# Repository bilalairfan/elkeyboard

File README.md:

# elkeyboard

A 3x3 macropad I will primarily use for CADding and school work.

## Features
- 8 keys
- a rotary encoder
- 128x32 OLED display
- LEDs under each key

link to cad: https://cad.onshape.com/documents/f6566b1274e7edd1fcbf8569/w/f5617eb1dfdd9ed77d1d4c33/e/8ab57a133af5eb0a263a87d2?renderMode=0&uiState=69e41b9765a285248c64cd51

# Diagrams

### Schematic: 

### PCB: 

## Firmware
My layout is going to be based on my shortcuts for my cad software (onshape).
The bottom line is going to be general purpose shortcuts while the top
and middle are more specific to working on onshape. This is primarily
sketch constraints as I tend to forget my binds when I'm working. 
Additionally, I have an encoder binded to my volume as I tend to change my volume a lot between days and tasks.

## BOM:
- 8x cherry mx switches
- 8x keycaps
- 1x ec11 rotary encoder
- 9x sk6812 mini e
- 9x 1N4148 diodes
- 1x OLED .91" 128x32
- 1x XIAO RP2040
- 1x case

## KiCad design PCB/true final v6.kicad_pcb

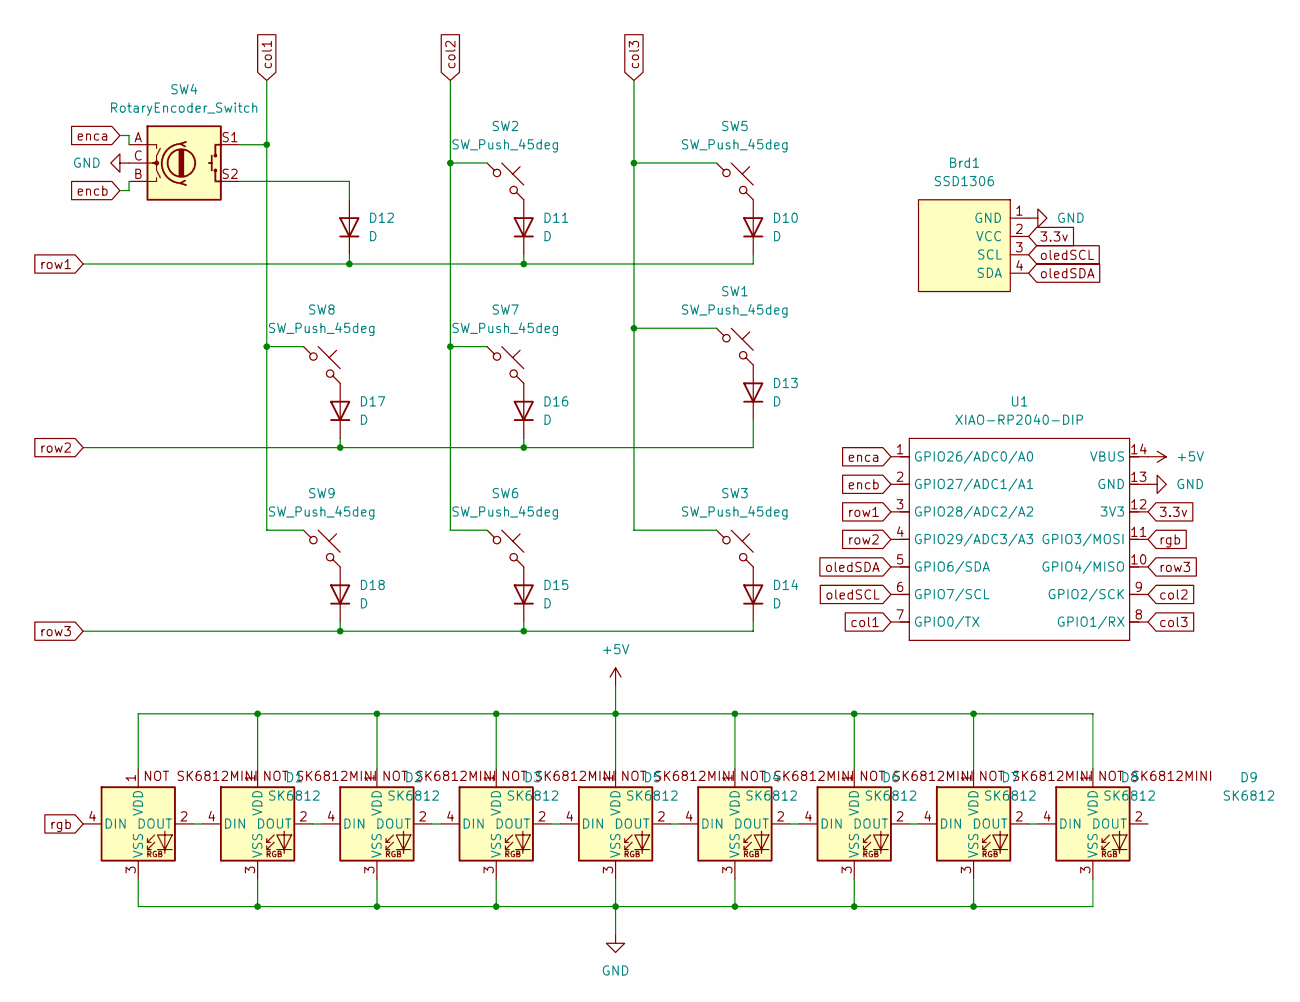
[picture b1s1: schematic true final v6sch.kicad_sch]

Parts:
Brd1: SSD1306; SSD1306-0.91-OLED-4pin-128x32
D1, D2, D3, D4, D5, D6, D7, D8, D9: SK6812; SK6812MINI-E_fixed
D10, D11, D12, D13, D14, D15, D16, D17, D18: D; D_DO-35_SOD27_P7.62mm_Horizontal
SW1, SW2, SW3, SW5, SW6, SW7, SW8, SW9: SW_Push_45deg; SW_Cherry_MX_1.00u_PCB
SW4: RotaryEncoder_Switch; RotaryEncoder_Alps_EC11E-Switch_Vertical_H20mm
U1: XIAO-RP2040-DIP

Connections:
3.3v: Brd1.2 (VCC), U1.12 (3V3)
+5V: D1.1 (VDD), D2.1 (VDD), D3.1 (VDD), D4.1 (VDD), D5.1 (VDD), D6.1 (VDD), D7.1 (VDD), D8.1 (VDD), D9.1 (VDD), U1.14 (VBUS)
GND: Brd1.1 (GND), D1.3 (VSS), D2.3 (VSS), D3.3 (VSS), D4.3 (VSS), D5.3 (VSS), D6.3 (VSS), D7.3 (VSS), D8.3 (VSS), D9.3 (VSS), SW4.C, U1.13 (GND)
unnamed: D1.2 (DOUT), D2.4 (DIN)
unnamed: D2.2 (DOUT), D3.4 (DIN)
unnamed: D3.2 (DOUT), D5.4 (DIN)
unnamed: D4.4 (DIN), D5.2 (DOUT)
unnamed: D4.2 (DOUT), D6.4 (DIN)
unnamed: D6.2 (DOUT), D7.4 (DIN)
unnamed: D7.2 (DOUT), D8.4 (DIN)
unnamed: D8.2 (DOUT), D9.4 (DIN)
unnamed: D10.2 (A), SW5.2
unnamed: D11.2 (A), SW2.2
unnamed: D12.2 (A), SW4.S2
unnamed: D13.2 (A), SW1.2
unnamed: D14.2 (A), SW3.2
unnamed: D15.2 (A), SW6.2
unnamed: D16.2 (A), SW7.2
unnamed: D17.2 (A), SW8.2
unnamed: D18.2 (A), SW9.2
col1: SW4.S1, SW8.1, SW9.1, U1.7 (GPIO0/TX)
col2: SW2.1, SW6.1, SW7.1, U1.9 (GPIO2/SCK)
col3: SW1.1, SW3.1, SW5.1, U1.8 (GPIO1/RX)
enca: SW4.A, U1.1 (GPIO26/ADC0/A0)
encb: SW4.B, U1.2 (GPIO27/ADC1/A1)
oledSCL: Brd1.3 (SCL), U1.6 (GPIO7/SCL)
oledSDA: Brd1.4 (SDA), U1.5 (GPIO6/SDA)
rgb: D1.4 (DIN), U1.11 (GPIO3/MOSI)
row1: D10.1 (K), D11.1 (K), D12.1 (K), U1.3 (GPIO28/ADC2/A2)
row2: D13.1 (K), D16.1 (K), D17.1 (K), U1.4 (GPIO29/ADC3/A3)
row3: D14.1 (K), D15.1 (K), D18.1 (K), U1.10 (GPIO4/MISO)

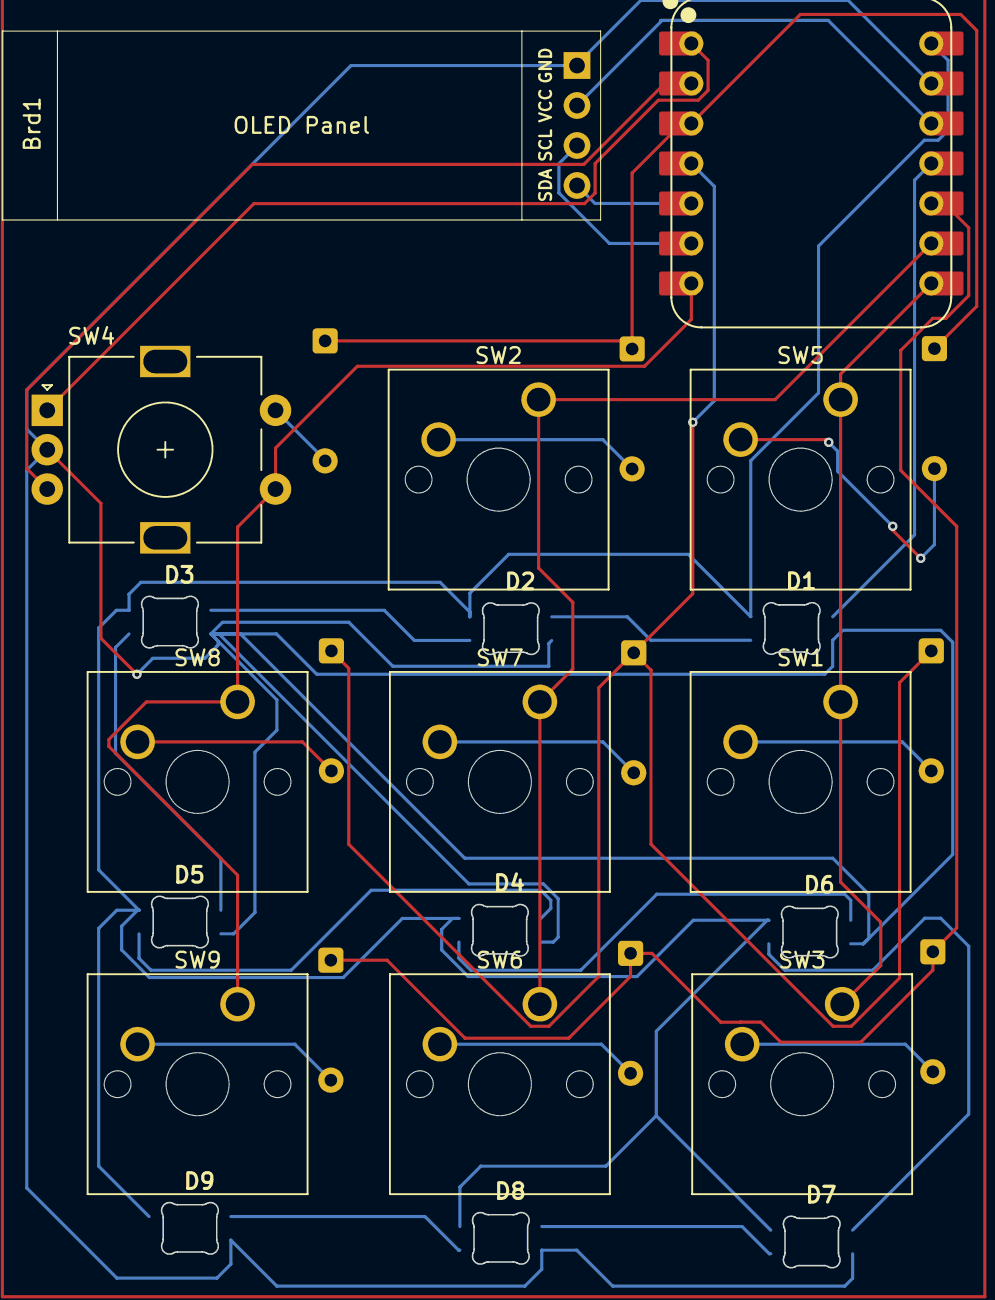
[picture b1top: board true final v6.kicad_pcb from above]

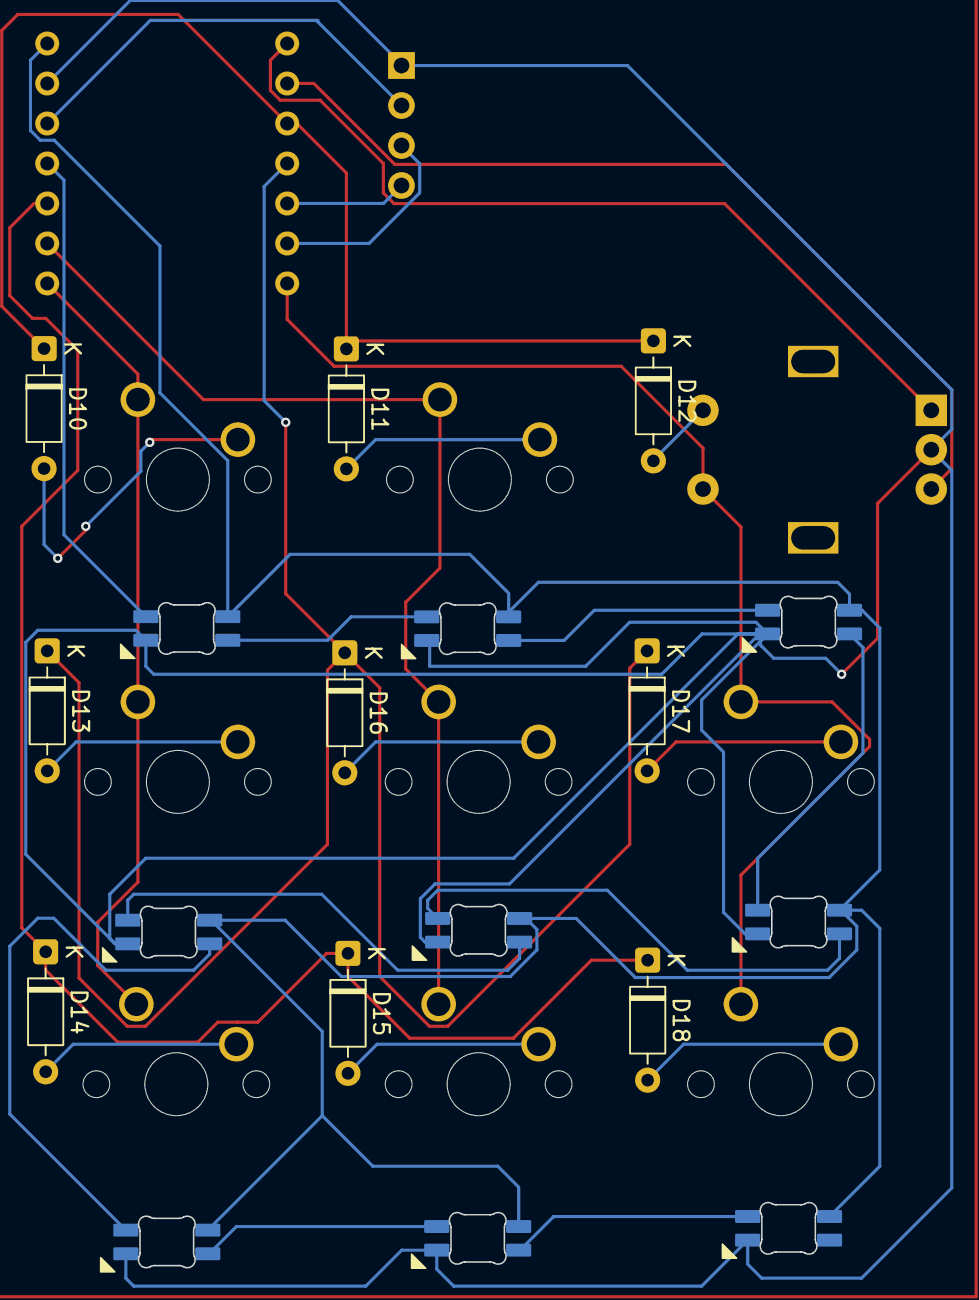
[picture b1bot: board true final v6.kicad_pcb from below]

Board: 2 copper layers, 29 parts (9 on the bottom side), 31 nets.

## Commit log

2026-03-31 Create e
2026-03-31 Create r
2026-03-31 Create f
2026-03-31 Create p
2026-03-31 Rename true final v5.step to elkeyboard.step
2026-03-31 Rename config.h.txt to production/config.h.txt
2026-03-31 Rename config.h.txt to config.h.txt
2026-03-31 Rename keymap.c to firmware/keymap.c
2026-03-31 Rename keymap.c to keymap.c
2026-03-31 Rename rules.mk.txt to Firmware/rules.mk.txt
